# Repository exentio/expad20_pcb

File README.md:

# ExPad20
This is the PCB for the macro pad firmware I put on in the **exentio/expad20_firm** repo, since the handwire design has a lot of flaws, cause the case I made is pure shit and the plate I bought doesn't have enough space on the borders

**IT'S WORKING FINE, BUT IT'S A BIT OF A MESS SO BE CAREFUL**

Shoutout to DirtyPCBs.com, I ordered there the PCBs, great prices and helpful resources and tools

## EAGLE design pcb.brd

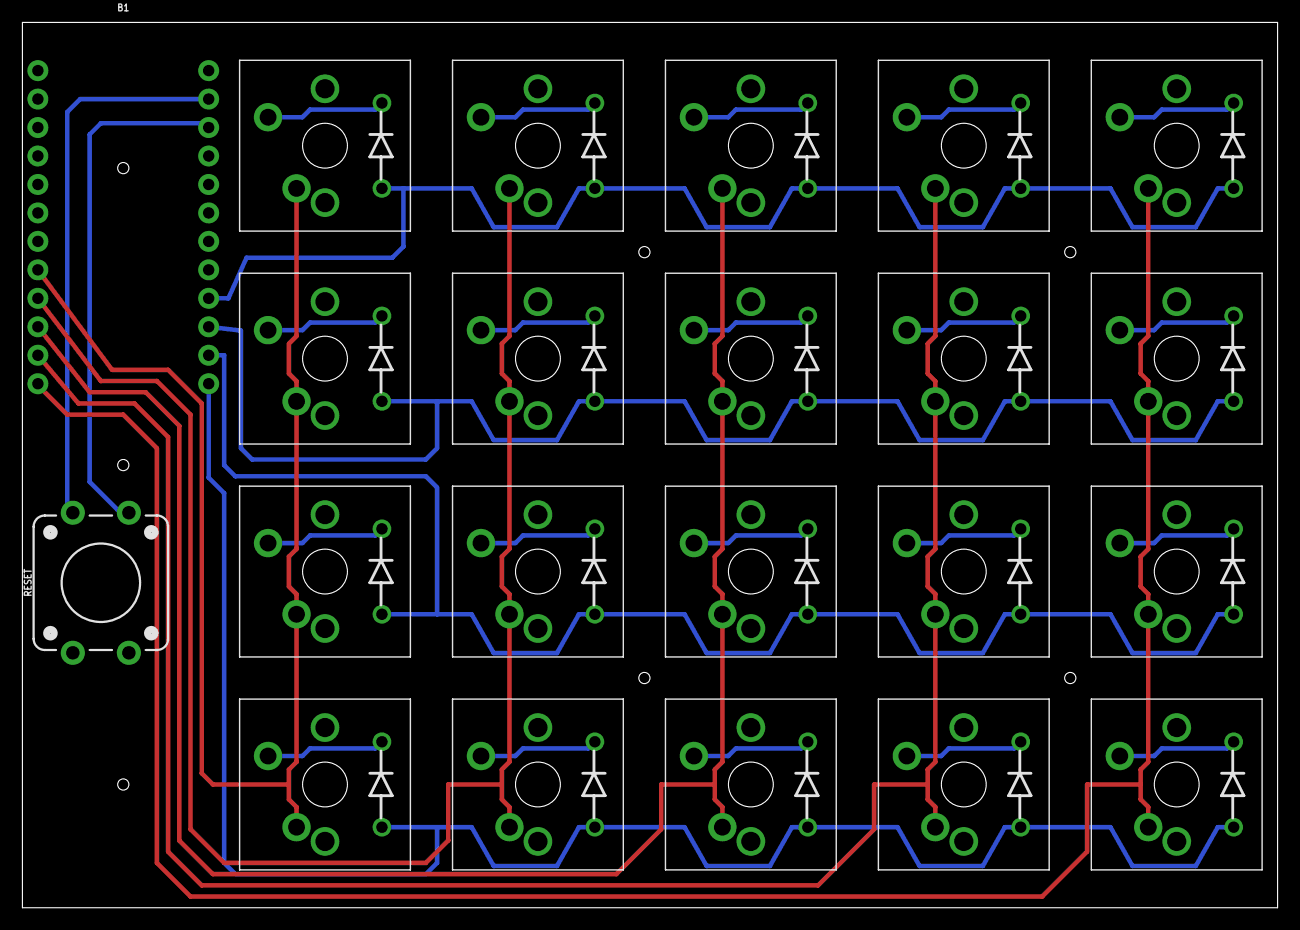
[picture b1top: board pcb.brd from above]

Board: 2 copper layers, 112.0 x 79.0 mm, 22 parts (0 on the bottom side), 32 nets.

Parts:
B1: Pro Micro; SPARKFUN_PRO_MICRO
RESET: RESET; TACTILE_SWITCH_PTH_12MM
U$1, U$2, U$3, U$4, U$5, U$6, U$7, U$8, U$9, U$10, U$11, U$12, U$13, U$14, U$15, U$16, U$17, U$18, U$19, U$20: CHERRY-MX-DIODE

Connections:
GND: B1.3, B1.4
unnamed: B1.9, U$2.SW1, U$7.SW1, U$12.SW1, U$17.SW1
unnamed: B1.23, RESET.3
unnamed: U$2.D2, U$2.SW2
unnamed: U$7.D2, U$7.SW2
unnamed: U$12.D2, U$12.SW2
unnamed: U$17.D2, U$17.SW2
unnamed: U$1.D2, U$1.SW2
unnamed: U$6.D2, U$6.SW2
unnamed: U$11.D2, U$11.SW2
unnamed: U$16.D2, U$16.SW2
unnamed: U$3.D2, U$3.SW2
unnamed: U$8.D2, U$8.SW2
unnamed: U$13.D2, U$13.SW2
unnamed: U$18.D2, U$18.SW2
unnamed: U$4.D2, U$4.SW2
unnamed: U$9.D2, U$9.SW2
unnamed: U$14.D2, U$14.SW2
unnamed: U$19.D2, U$19.SW2
unnamed: U$5.D2, U$5.SW2
unnamed: U$10.D2, U$10.SW2
unnamed: U$15.D2, U$15.SW2
unnamed: U$20.D2, U$20.SW2
unnamed: B1.22, RESET.1
unnamed: B1.10, U$3.SW1, U$8.SW1, U$13.SW1, U$18.SW1
unnamed: B1.13, U$16.D1, U$17.D1, U$18.D1, U$19.D1, U$20.D1
unnamed: B1.15, U$6.D1, U$7.D1, U$8.D1, U$9.D1, U$10.D1
unnamed: B1.14, U$11.D1, U$12.D1, U$13.D1, U$14.D1, U$15.D1
unnamed: B1.16, U$1.D1, U$2.D1, U$3.D1, U$4.D1, U$5.D1
S$1: U$4.SW1, U$9.SW1, U$14.SW1, U$19.SW1
S$2: U$5.SW1, U$10.SW1, U$15.SW1, U$20.SW1
S$3: U$1.SW1, U$6.SW1, U$11.SW1, U$16.SW1

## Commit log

2017-04-16 Minor enhancements
2017-04-17 Final design; ordered
2017-04-17 Readme, cleanup
2017-07-07 Yay it works

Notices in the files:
parts and their libraries:
SparkFun-Boards: Licensing: Creative Commons ShareAlike 4.0 International - https://creativecommons.org/licenses/by-sa/4.0
